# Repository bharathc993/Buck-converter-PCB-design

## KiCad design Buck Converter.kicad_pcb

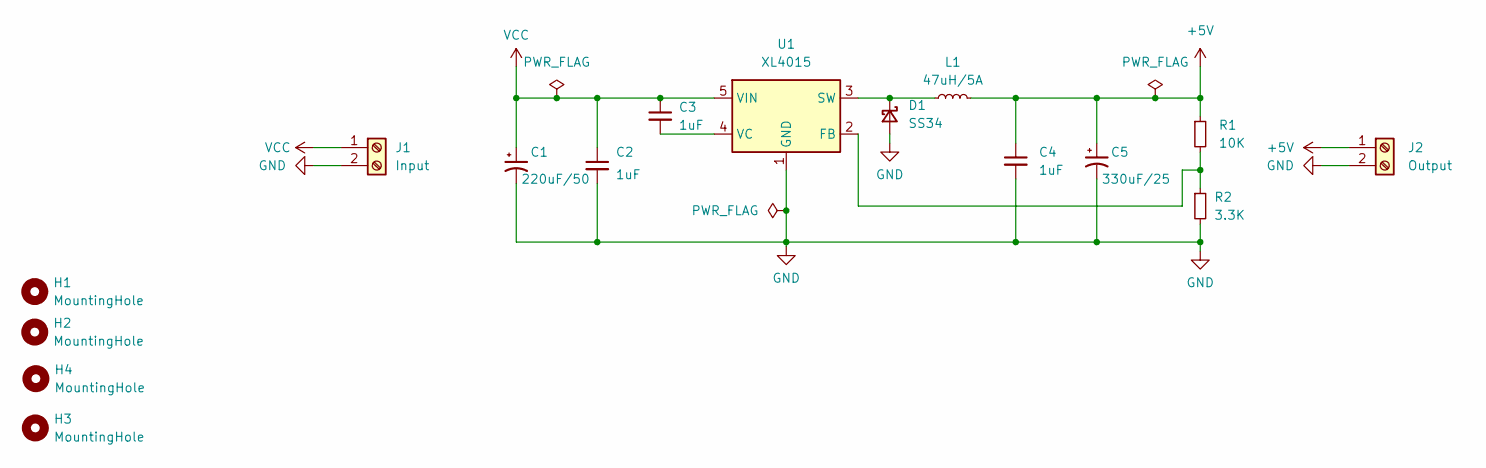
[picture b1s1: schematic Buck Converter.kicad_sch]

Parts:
C1: 220uF/50; CP_Elec_10x10
C2, C3, C4: 1uF; C_0603_1608Metric
C5: 330uF/25; CP_Elec_10x10
D1: SS34; D_SMA
H1, H2, H3, H4: MountingHole; MountingHole_2.1mm
J1: Input; Altech_AK300_1x02_P5.00mm_45-Degree
J2: Output; Altech_AK300_1x02_P5.00mm_45-Degree
L1: 47uH/5A; L_Bourns_SRR1260
R1: 10K; R_0603_1608Metric
R2: 3.3K; R_0603_1608Metric
U1: XL4015; TO-263-5_TabPin6

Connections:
+5V: C4.1, C5.1, J2.1, L1.2, R1.1
GND: C1.2, C2.2, C4.2, C5.2, D1.2 (A), J1.2, J2.2, R2.2, U1.1 (GND)
unnamed: D1.1 (K), L1.1, U1.3 (SW)
unnamed: R1.2, R2.1, U1.2 (FB)
unnamed: C3.2, U1.4 (VC)
VCC: C1.1, C2.1, C3.1, J1.1, U1.5 (VIN)

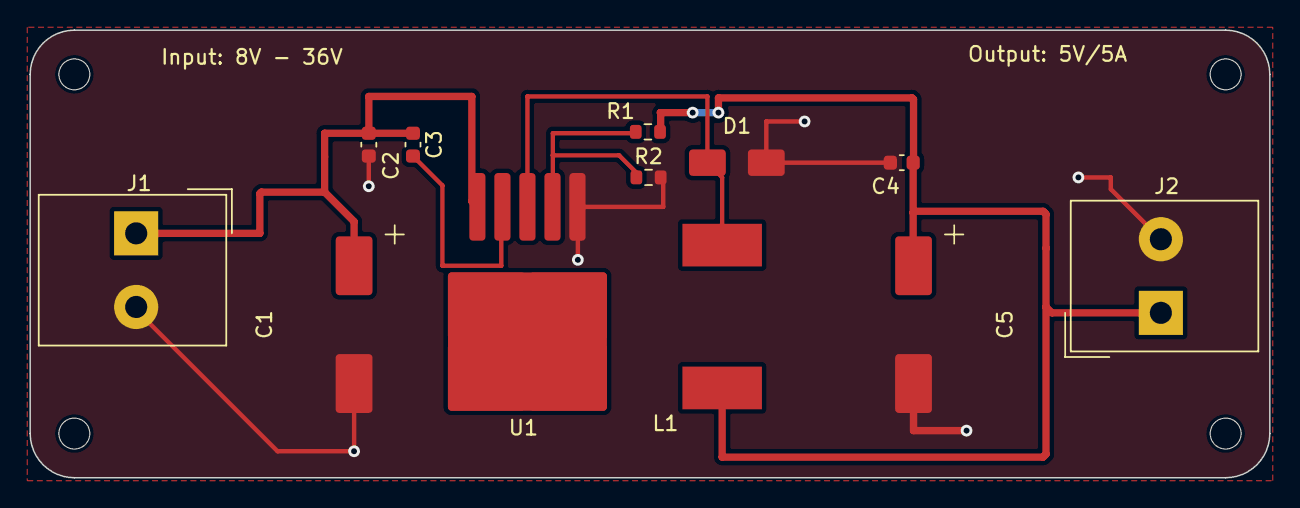
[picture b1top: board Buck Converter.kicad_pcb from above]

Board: 2 copper layers, 84.2 x 30.4 mm, 16 parts (0 on the bottom side), 6 nets.
